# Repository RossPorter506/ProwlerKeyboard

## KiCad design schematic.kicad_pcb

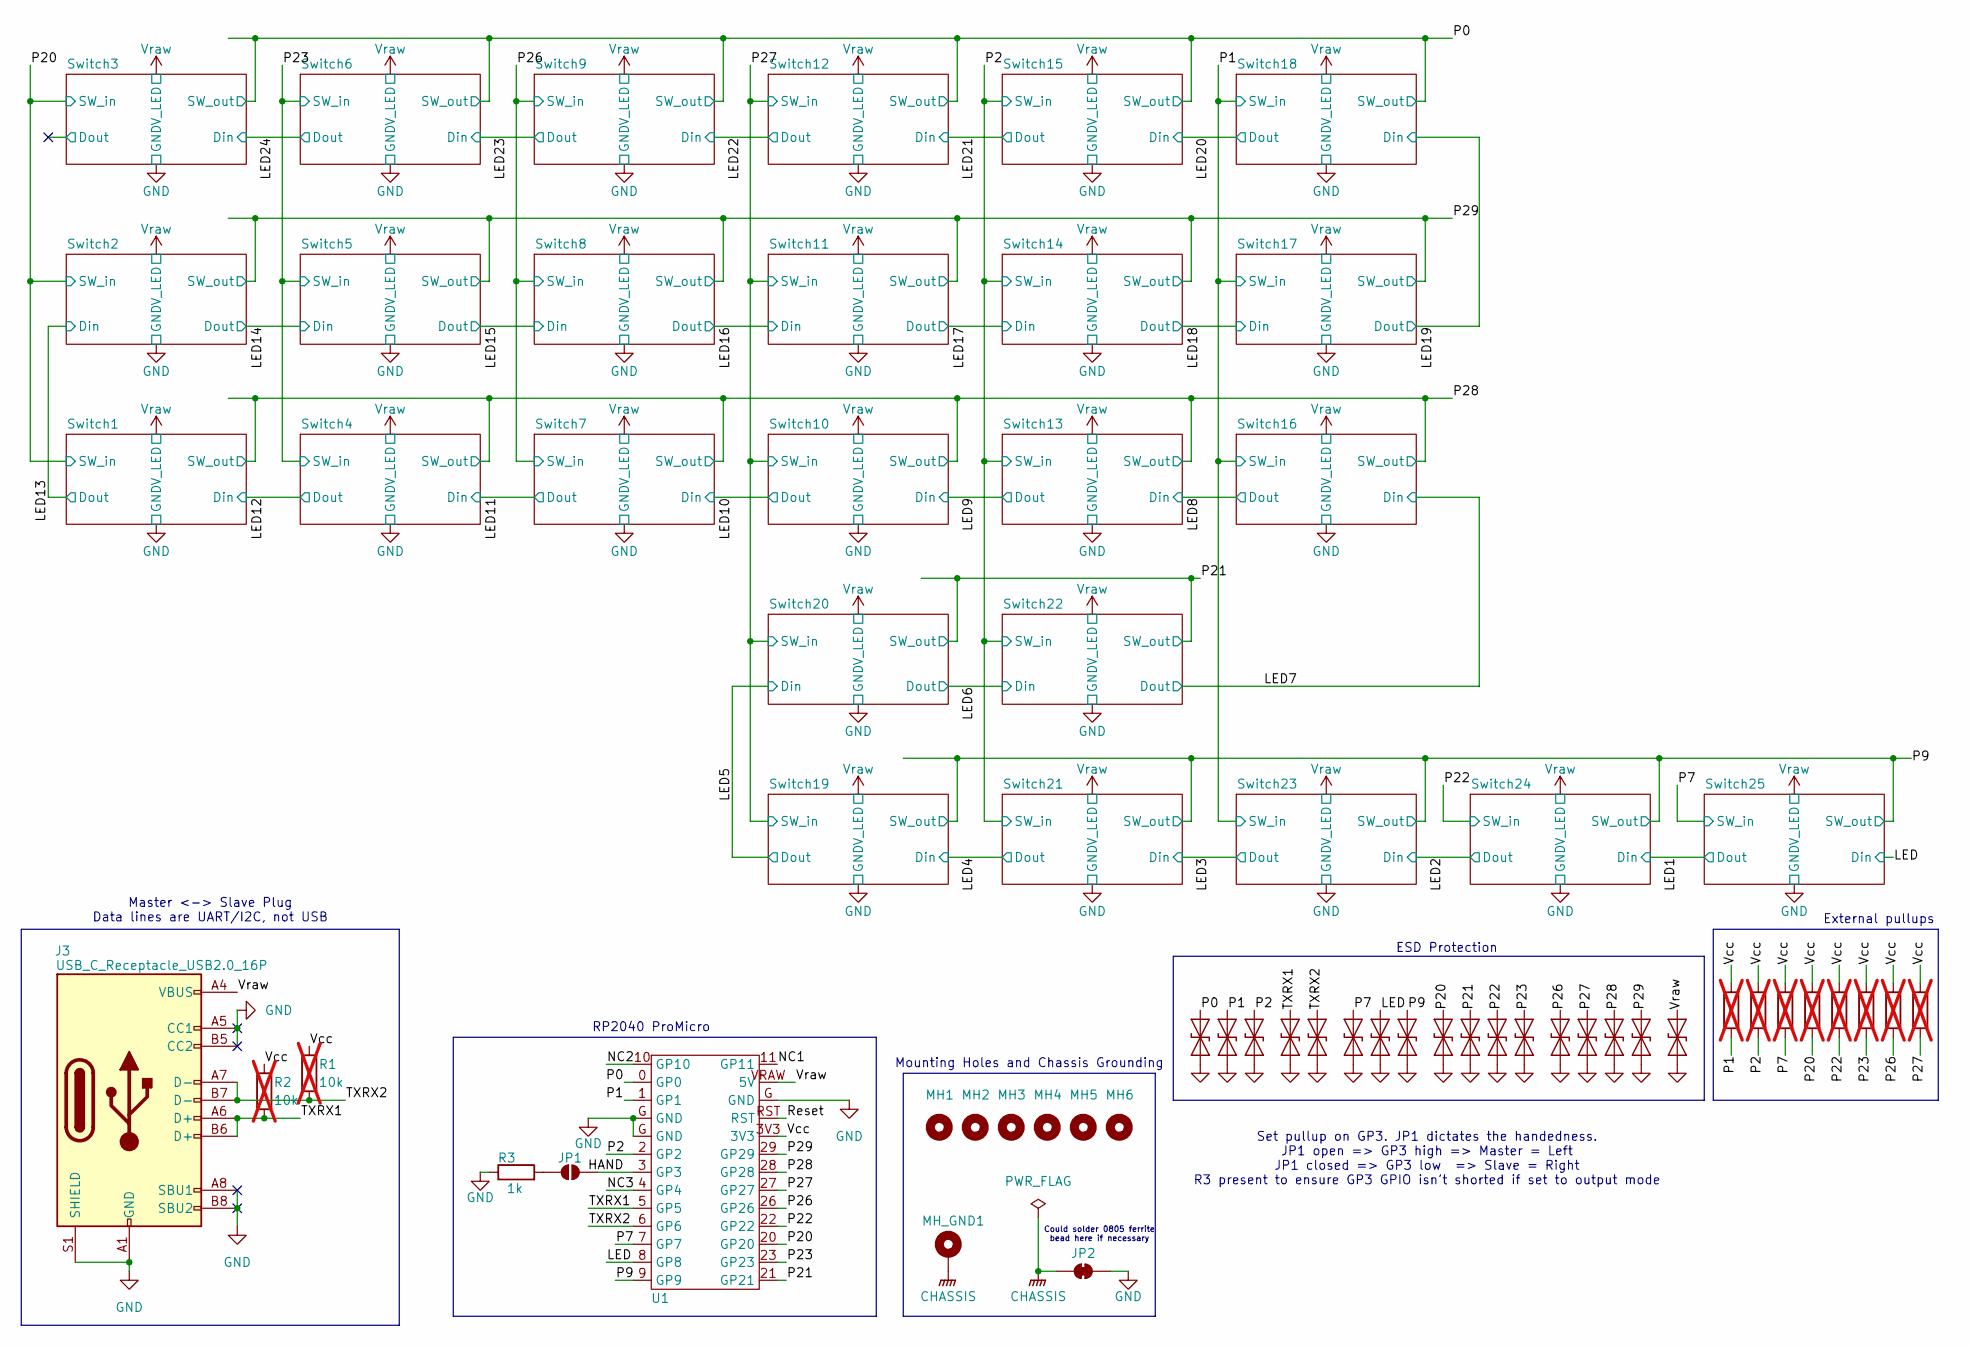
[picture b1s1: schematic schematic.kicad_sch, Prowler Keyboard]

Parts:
D26, D27, D28, D29, D30, D31, D32, D33, D34, D35, D36, D37, D38, D39, D40, D41, D42: ESD5Z5.0C; D_SOD-523
J3: USB_C_Receptacle_USB2.0_16P; USB_C_Receptacle_GCT_USB4105-xx-A_16P_TopMnt_Horizontal
JP1: SolderJumper_2_Open; SolderJumper-2_P1.3mm_Open_RoundedPad1.0x1.5mm
JP2: SolderJumper_2_Bridged; SolderJumper-2_P1.3mm_Bridged_RoundedPad1.0x1.5mm
MH1, MH2, MH3, MH4, MH5, MH6: MountingHole_Pad; MountingHole_3mm_Pad_Via
MH_GND1: MountingHole_Pad; MountingHole_3mm_Pad_Via
R1, R2, R4, R5, R6, R7, R8, R9, R10, R11: 10k; R_0805_2012Metric_Pad1.20x1.40mm_HandSolder; not fitted
R3: 1k; R_0805_2012Metric_Pad1.20x1.40mm_HandSolder
U1: RP2040ProMicroCloneReversible

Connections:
/HAND: JP1.1 (A), U1.3 (GP3)
/LED: D32.2 (A2), U1.8 (GP8); also elsewhere on the board
/NC1: U1.11 (GP11)
/NC2: U1.10 (GP10)
/NC3: U1.4 (GP4)
/P0: D26.2 (A2), U1.0 (GP0); also elsewhere on the board
/P1: D27.2 (A2), R11.2, U1.1 (GP1); also elsewhere on the board
/P2: D28.2 (A2), R4.2, U1.2 (GP2); also elsewhere on the board
/P7: D31.2 (A2), R5.2, U1.7 (GP7); also elsewhere on the board
/P9: D33.2 (A2), U1.9 (GP9); also elsewhere on the board
/P20: D34.2 (A2), R6.2, U1.20 (GP20); also elsewhere on the board
/P21: D35.2 (A2), U1.21 (GP21); also elsewhere on the board
/P22: D36.2 (A2), R7.2, U1.22 (GP22); also elsewhere on the board
/P23: D37.2 (A2), R8.2, U1.23 (GP23); also elsewhere on the board
/P26: D38.2 (A2), R9.2, U1.26 (GP26); also elsewhere on the board
/P27: D39.2 (A2), R10.2, U1.27 (GP27); also elsewhere on the board
/P28: D40.2 (A2), U1.28 (GP28); also elsewhere on the board
/P29: D41.2 (A2), U1.29 (GP29); also elsewhere on the board
/Reset: U1.RST
/TXRX1: D29.2 (A2), J3.A6 (D+), J3.B6 (D+), R2.2, U1.5 (GP5)
/TXRX2: D30.2 (A2), J3.A7 (D-), J3.B7 (D-), R1.2, U1.6 (GP6)
/Vcc: R1.1, R2.1, R4.1, R5.1, R6.1, R7.1, R8.1, R9.1, R10.1, R11.1, U1.3V3
CHASSIS: JP2.1 (A), MH_GND1.1
GND: D26.1 (A1), D27.1 (A1), D28.1 (A1), D29.1 (A1), D30.1 (A1), D31.1 (A1), D32.1 (A1), D33.1 (A1), D34.1 (A1), D35.1 (A1), D36.1 (A1), D37.1 (A1), D38.1 (A1), D39.1 (A1), D40.1 (A1), D41.1 (A1), D42.1 (A1), J3.A1 (GND), J3.A5 (CC1), J3.A8 (SBU1), J3.A12 (GND), J3.B1 (GND), J3.B5 (CC2), J3.B8 (SBU2), J3.B12 (GND), J3.S1 (SHIELD), JP2.2 (B), R3.1, U1.G (GND); also elsewhere on the board
unnamed: JP1.2 (B), R3.2
Vraw: D42.2 (A2), J3.A4 (VBUS), J3.A9 (VBUS), J3.B4 (VBUS), J3.B9 (VBUS), U1.VRAW (5V); also elsewhere on the board

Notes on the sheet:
Could solder 0805 ferrite bead here if necessary
Mounting Holes and Chassis Grounding
RP2040 ProMicro
External pullups
Master <-> Slave Plug Data lines are UART/I2C, not USB
ESD Protection
Set pullup on GP3. JP1 dictates the handedness. JP1 open => GP3 high => Master = Left JP1 closed => GP3 low => Slave = Right R3 present to ensure GP3 GPIO isn't shorted if set to output mode

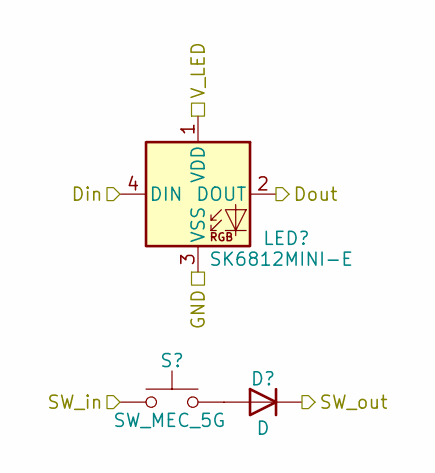
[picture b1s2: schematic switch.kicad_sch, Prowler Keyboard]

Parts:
D22: D; ComboDiode
LED22: SK6812MINI-E; SK6812MINI-E_RVRSMOUNT
S22: SW_MEC_5G; MX

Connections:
/LED6: LED22.4 (DIN); also elsewhere on the board
/LED7: LED22.2 (DOUT); also elsewhere on the board
/P2: S22.1 (A); also elsewhere on the board
/P21: D22.1 (K); also elsewhere on the board
GND: LED22.3 (VSS); also elsewhere on the board
unnamed: D22.2 (A), S22.2 (B)
Vraw: LED22.1 (VDD); also elsewhere on the board

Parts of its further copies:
D1, D2, D3, D4, D5, D6, D7, D8, D9, D10, D11, D12, D13, D14, D15, D16, D17, D18, D19, D20, D21, D23, D24, D25: D; ComboDiode
LED1, LED2, LED3, LED4, LED5, LED6, LED7, LED8, LED9, LED10, LED11, LED12, LED13, LED14, LED15, LED16, LED17, LED18, LED19, LED20, LED21, LED23, LED24, LED25: SK6812MINI-E; SK6812MINI-E_RVRSMOUNT
S1, S2, S3, S4, S5, S6, S7, S8, S9, S10, S11, S12, S13, S14, S15, S16, S17, S18, S19, S20, S21, S23, S24, S25: SW_MEC_5G; MX

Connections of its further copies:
/LED: LED25.4 (DIN); also elsewhere on the board
/LED1: LED24.4 (DIN), LED25.2 (DOUT)
/LED2: LED23.4 (DIN), LED24.2 (DOUT)
/LED3: LED21.4 (DIN), LED23.2 (DOUT)
/LED4: LED19.4 (DIN), LED21.2 (DOUT)
/LED5: LED19.2 (DOUT), LED20.4 (DIN)
/LED6: LED20.2 (DOUT); also elsewhere on the board
/LED7: LED16.4 (DIN); also elsewhere on the board
/LED8: LED13.4 (DIN), LED16.2 (DOUT)
/LED9: LED10.4 (DIN), LED13.2 (DOUT)
/LED10: LED7.4 (DIN), LED10.2 (DOUT)
/LED11: LED4.4 (DIN), LED7.2 (DOUT)
/LED12: LED1.4 (DIN), LED4.2 (DOUT)
/LED13: LED1.2 (DOUT), LED2.4 (DIN)
/LED14: LED2.2 (DOUT), LED5.4 (DIN)
/LED15: LED5.2 (DOUT), LED8.4 (DIN)
/LED16: LED8.2 (DOUT), LED11.4 (DIN)
/LED17: LED11.2 (DOUT), LED14.4 (DIN)
/LED18: LED14.2 (DOUT), LED17.4 (DIN)
/LED19: LED17.2 (DOUT), LED18.4 (DIN)
/LED20: LED15.4 (DIN), LED18.2 (DOUT)
/LED21: LED12.4 (DIN), LED15.2 (DOUT)
/LED22: LED9.4 (DIN), LED12.2 (DOUT)
/LED23: LED6.4 (DIN), LED9.2 (DOUT)
/LED24: LED3.4 (DIN), LED6.2 (DOUT)
/P0: D3.1 (K), D6.1 (K), D9.1 (K), D12.1 (K), D15.1 (K), D18.1 (K); also elsewhere on the board
/P1: S16.1 (A), S17.1 (A), S18.1 (A), S23.1 (A); also elsewhere on the board
/P2: S13.1 (A), S14.1 (A), S15.1 (A), S21.1 (A); also elsewhere on the board
/P7: S25.1 (A); also elsewhere on the board
/P9: D19.1 (K), D21.1 (K), D23.1 (K), D24.1 (K), D25.1 (K); also elsewhere on the board
/P20: S1.1 (A), S2.1 (A), S3.1 (A); also elsewhere on the board
/P21: D20.1 (K); also elsewhere on the board
/P22: S24.1 (A); also elsewhere on the board
/P23: S4.1 (A), S5.1 (A), S6.1 (A); also elsewhere on the board
/P26: S7.1 (A), S8.1 (A), S9.1 (A); also elsewhere on the board
/P27: S10.1 (A), S11.1 (A), S12.1 (A), S19.1 (A), S20.1 (A); also elsewhere on the board
/P28: D1.1 (K), D4.1 (K), D7.1 (K), D10.1 (K), D13.1 (K), D16.1 (K); also elsewhere on the board
/P29: D2.1 (K), D5.1 (K), D8.1 (K), D11.1 (K), D14.1 (K), D17.1 (K); also elsewhere on the board
/Switch3/Dout: LED3.2 (DOUT)
/Switch3/Dout_1: LED3.2 (DOUT)
GND: LED1.3 (VSS), LED2.3 (VSS), LED3.3 (VSS), LED4.3 (VSS), LED5.3 (VSS), LED6.3 (VSS), LED7.3 (VSS), LED8.3 (VSS), LED9.3 (VSS), LED10.3 (VSS), LED11.3 (VSS), LED12.3 (VSS), LED13.3 (VSS), LED14.3 (VSS), LED15.3 (VSS), LED16.3 (VSS), LED17.3 (VSS), LED18.3 (VSS), LED19.3 (VSS), LED20.3 (VSS), LED21.3 (VSS), LED23.3 (VSS), LED24.3 (VSS), LED25.3 (VSS); also elsewhere on the board
unnamed: D1.2 (A), S1.2 (B)
unnamed: D2.2 (A), S2.2 (B)
unnamed: D3.2 (A), S3.2 (B)
unnamed: D4.2 (A), S4.2 (B)
unnamed: D5.2 (A), S5.2 (B)
unnamed: D6.2 (A), S6.2 (B)
unnamed: D7.2 (A), S7.2 (B)
unnamed: D8.2 (A), S8.2 (B)
unnamed: D9.2 (A), S9.2 (B)
unnamed: D10.2 (A), S10.2 (B)
unnamed: D11.2 (A), S11.2 (B)
unnamed: D12.2 (A), S12.2 (B)
unnamed: D13.2 (A), S13.2 (B)
unnamed: D14.2 (A), S14.2 (B)
unnamed: D15.2 (A), S15.2 (B)
unnamed: D16.2 (A), S16.2 (B)
unnamed: D17.2 (A), S17.2 (B)
unnamed: D18.2 (A), S18.2 (B)
unnamed: D19.2 (A), S19.2 (B)
unnamed: D20.2 (A), S20.2 (B)
unnamed: D21.2 (A), S21.2 (B)
unnamed: D23.2 (A), S23.2 (B)
unnamed: D24.2 (A), S24.2 (B)
unnamed: D25.2 (A), S25.2 (B)
Vraw: LED1.1 (VDD), LED2.1 (VDD), LED3.1 (VDD), LED4.1 (VDD), LED5.1 (VDD), LED6.1 (VDD), LED7.1 (VDD), LED8.1 (VDD), LED9.1 (VDD), LED10.1 (VDD), LED11.1 (VDD), LED12.1 (VDD), LED13.1 (VDD), LED14.1 (VDD), LED15.1 (VDD), LED16.1 (VDD), LED17.1 (VDD), LED18.1 (VDD), LED19.1 (VDD), LED20.1 (VDD), LED21.1 (VDD), LED23.1 (VDD), LED24.1 (VDD), LED25.1 (VDD); also elsewhere on the board

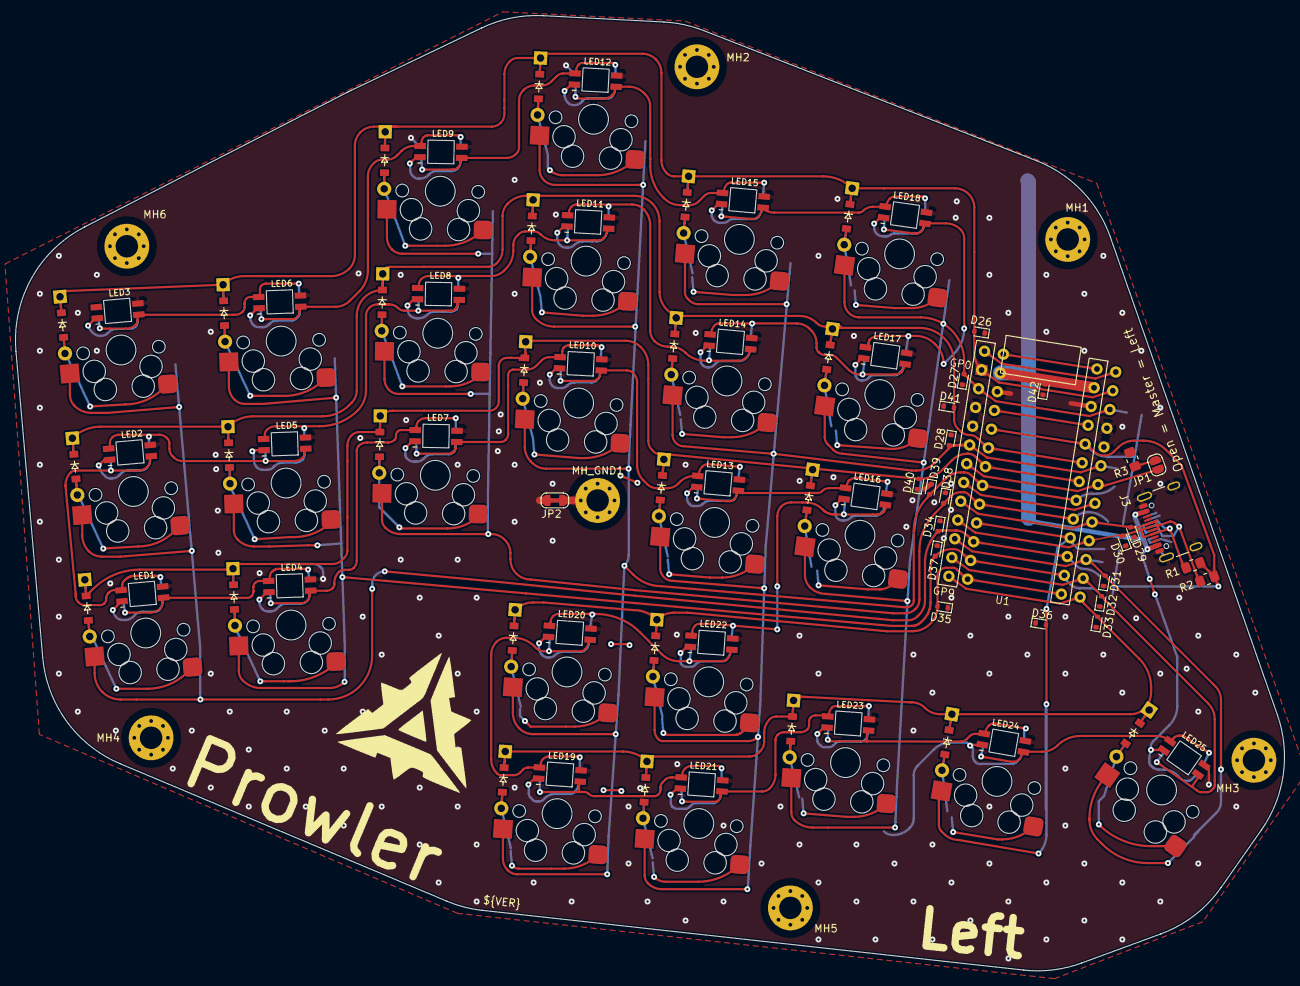
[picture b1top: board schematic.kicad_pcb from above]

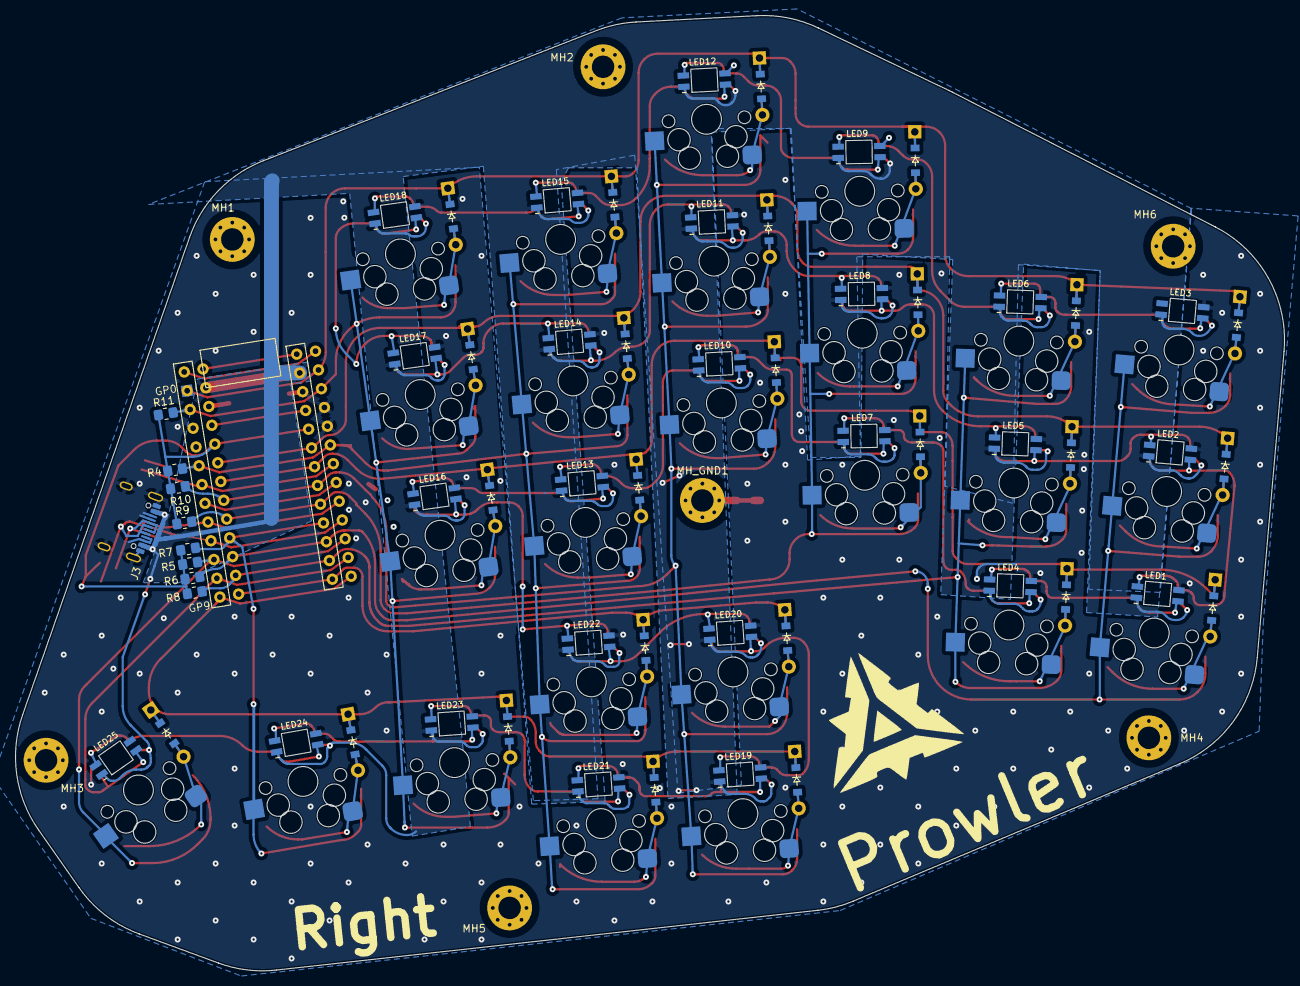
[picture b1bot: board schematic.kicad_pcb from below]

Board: 2 copper layers, 169.7 x 127.8 mm, 114 parts (8 on the bottom side), 71 nets.

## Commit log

2024-12-29 v1.1.0: Add stabilizers to 2u keys
2024-12-29 v1.0.0: Update title block, add project version variable
2024-12-30 Reorganise root folder
2024-12-30 Add QMK 3x6 split template
2024-12-30 Fix disconnected pours
2024-12-30 Begin firmware configuration
2024-12-31 Add x,y key positions, start keymap
2025-01-01 Initial keymap and key overrides
    Not sure if these key overrides will work, considering some of them are to do with the shift key and shifted keycodes.
2025-01-01 Initial RGB matrix map
2025-01-03 First compile
    Remove physically absent pins from keymap.
    Add key_override in info.json, not rules.mk.
    Use PIO for serial, ws2812 driver.
    Can't figure out how to set internal pullup on handedness pin, instead use USB detect..
2025-01-03 Widen MCU header holes slightly
    The holes were a big snug, widen from 0.7mm -> 1.0mm.
2025-01-03 Configure full duplex serial, enable debug logging Seems like the two controllers can talk to eachother, at least
2025-01-03 Set pullup on handedness pin Also swap handedness detection to pin
2025-01-10 Put other hand keymap after first hand, rather than interleaved
2025-01-11 Disambiguate SK6812 pin indicator Use a cutout pad to signify the cutout pin, rather than a dash for pin 1. The initial instinct is to line the dash with the cutout pin, but this is wrong as the cuto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
2025-01-18 Fix key ordering
    Synchronise order of keyboard.json matrix with LAYOUT macro. Take the opportunity to revert the one-after-the-other approach in keymap.c now that I understand the whole thing better.
2025-01-18 Fix LED ordering
2025-01-18 Add RGB keybinds, layer enum
2025-01-22 Tweak keymap
2025-01-31 Add ergogen plate definition, move RP2040 footprint to project lib
